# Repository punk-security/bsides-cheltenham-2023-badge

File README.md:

# bsides-cheltenham-2023-badge
The Delorean badge for BSIDES Cheltenham 2023!

We raised over £300 for Mind charity selling parts to complete these on the day!!!!

## Bill Of Materials

You can see a parts list on DigiKey [here](https://www.digikey.co.uk/en/mylists/list/DBJ9N5IB9O)

Essentially its:

* ATTINY402 microcontroller - any spec 402 will do
* Button - any surface mount button fitting the footprint will work
* CR2032 battery clip - surface mount not through hole
* Neopixel addressable LED - Definitely get the right version of these
* Any 3528 Blue LED will work for the bumper rail

## Eagle designs and ordering your own badge

We've uploaded the AutoCAD EAGLE schematic, board design and custom footprints so you can make your own variants!  You will probably have to do some tweaks to get it working as they're designed to be standalone exports.

We've also uploaded the gerber_files.zip.  Take this to JLCPCB and you can order your own exact copies of the board :)

## Writing and flashing code!

We use [MegaTinyCore](https://github.com/SpenceKonde/megaTinyCore) for the arduino interface for ATTINY4x2 chips.

Dev and flashing is done within the Arduino IDE ( < v2 ) using a jtag2updi interface, as discussed [here](https://github.com/SpenceKonde/AVR-Guidance/blob/master/UPDI/jtag2updi.md)

We use [these little usb sticks](https://amzn.eu/d/c0lx0wG), with a 4.7k resistor soldered between the Tx and Rx lines.  

### Installing MegaTinyCore dependencies

This board package can be installed via the board manager in arduino. The boards manager URL is:

`http://drazzy.com/package_drazzy.com_index.json`

1. File -> Preferences, enter the above URL in "Additional Boards Manager URLs"
2. Tools -> Boards -> Boards Manager...
3. Wait while the list loads (takes longer than one would expect, and refreshes several times).
4. Select "megaTinyCore by Spence Konde" and click "Install". For best results, choose the most recent version.

### Setting up the IDE

1. Open the file **bsides-cheltenham-2023-badge.ino** in arduino
2. Select tools > Board > megaTinyCore > ATtiny412/402/212/202
3. Select tools > Chip > ATtiny402
4. Select tools > Clock > 8Mhz internal *(we get power issues otherwise)*
5. Select tools > Programmer > SerialUPDI SLOW
6. Select tools > Port > ( pick your COM port)

### Flashing firmware
1. Connect the 3v3 pin to 3v on your usb (maybe wedge it in the battery clip)
2. Connect GND to GND
3. Connect UPDI to the RxD port
4. Click Upload button

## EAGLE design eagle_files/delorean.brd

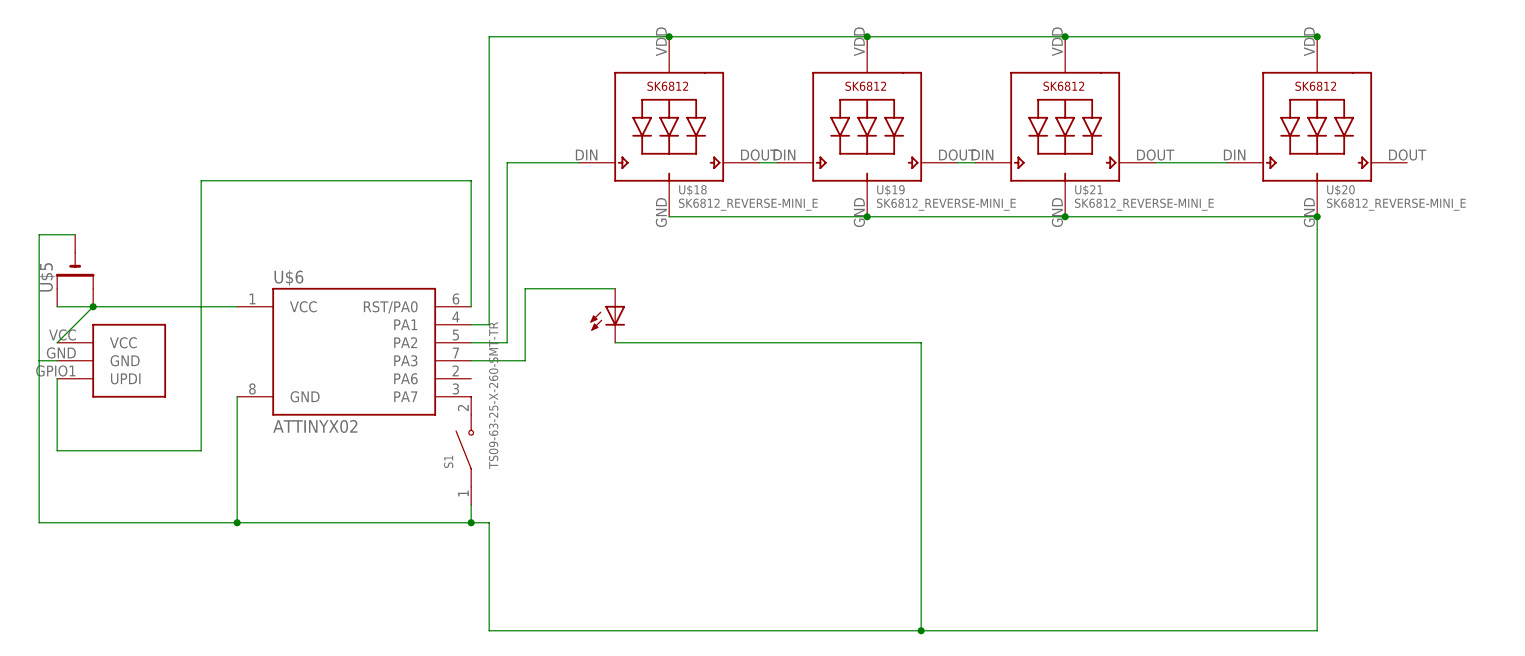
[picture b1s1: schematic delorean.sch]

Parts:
S1: TS09-63-25-X-260-SMT-TR; SW_TS09-63-25-X-260-SMT-TR
U$1: LED_SMD_REVERSEMOUNT3528; B/3528-21R
U$5: CR2032SMT; CR2032-SMD
U$6: ATTINYX02; SOIC08_JEDEC_150MIL
U$7: SAO; SAO_SMD
U$18, U$19, U$20, U$21: SK6812_REVERSE-MINI_E; SK6812-MINI-E

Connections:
GND: S1.1, U$1.+ (C), U$5.-, U$6.8 (GND), U$7.GND, U$18.GND, U$19.GND, U$20.GND, U$21.GND
LED: U$1.- (A), U$6.7 (PA3)
unnamed: U$6.6 (RST/PA0), U$7.GPIO1 (UPDI)
unnamed: U$5.+$1 (+), U$5.+$2 (+1), U$6.1 (VCC), U$7.VCC
unnamed: S1.2, U$6.3 (PA7)
unnamed: U$18.DOUT (DO), U$19.DIN (DI)
unnamed: U$6.4 (PA1), U$18.VDD, U$19.VDD, U$20.VDD, U$21.VDD
unnamed: U$6.5 (PA2), U$18.DIN (DI)
unnamed: U$19.DOUT (DO), U$21.DIN (DI)
unnamed: U$20.DIN (DI), U$21.DOUT (DO)

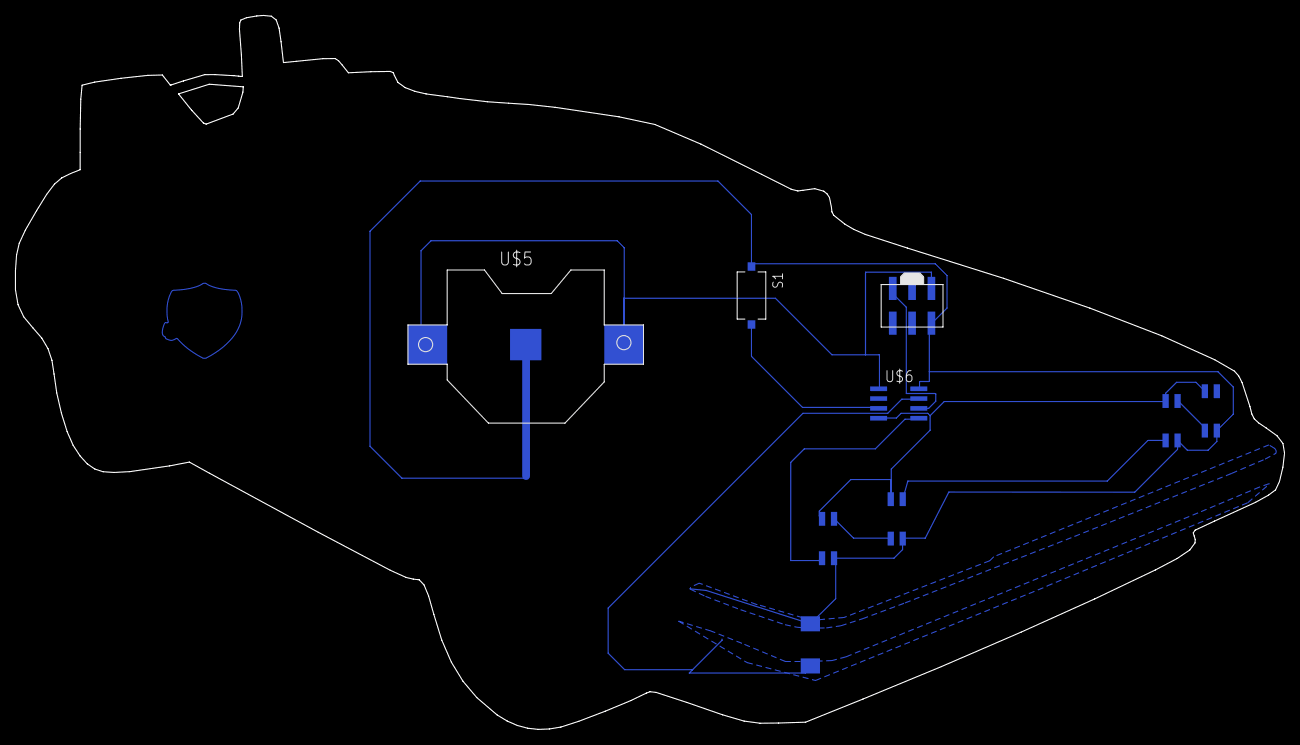
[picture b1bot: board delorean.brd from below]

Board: 2 copper layers, 164.2 x 92.4 mm, 9 parts (9 on the bottom side), 10 nets.

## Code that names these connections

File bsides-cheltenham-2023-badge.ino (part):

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#include <avr/sleep.h>
#include <tinyNeoPixel_Static.h>

#define BUTTON_PIN PIN_PA7
#define BUMPER_POWER PIN_PA3
#define HEADLIGHT_POWER PIN_PA1
#define HEADLIGHT_GPIO PIN_PA2

#define NUMLEDS 4
#define LEFT 0
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
void success()
{
  analogWrite(PIN_PA3, 255); // SET EEPROM
  for(int j = 0; j < 4; j++)
  {
    setAllPixels(0,255,0,true);
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    setAllPixels(0,0,0,true);
    delay(50);
  }
  analogWrite(PIN_PA3, 0); // SET EEPROM
  EEPROM.update(0, state);
  delay(200);
}

void fail()
{
  analogWrite(PIN_PA3, 255); // SET EEPROM
  for(int j = 0; j < 4; j++)
  {
    setAllPixels(255,0,0,true);
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    setAllPixels(0,0,0,true);
    delay(50);
  }
  analogWrite(PIN_PA3, 0); // SET EEPROM
  delay(200);
}

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  int i = n % (range * 2);
  if (i < range)
  {
    analogWrite(PIN_PA3, min + (i * step));
  }
  else
  {
    analogWrite(PIN_PA3, (max * 2) - (i * step));
  }
  return 100;
}
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    return;
    if(x % 2 == 0)
  {
    analogWrite(PIN_PA3,255);
  }
  else
  {
    analogWrite(PIN_PA3,0);
  }
}

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  pinMode(HEADLIGHT_POWER, OUTPUT);
  pinMode(HEADLIGHT_GPIO, OUTPUT);
  pinMode(BUMPER_POWER, OUTPUT);
  // UPDI does not need setting (PA0)

  // Pin setup
  pinMode(BUTTON_PIN, INPUT_PULLUP);
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
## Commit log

2023-06-01 init
2023-06-05 feat: add more info
2023-06-05 feat: add docs update and bom
2023-06-05 feat: add more info (#3)
    * feat: add more info
    * feat: add docs update and bom
